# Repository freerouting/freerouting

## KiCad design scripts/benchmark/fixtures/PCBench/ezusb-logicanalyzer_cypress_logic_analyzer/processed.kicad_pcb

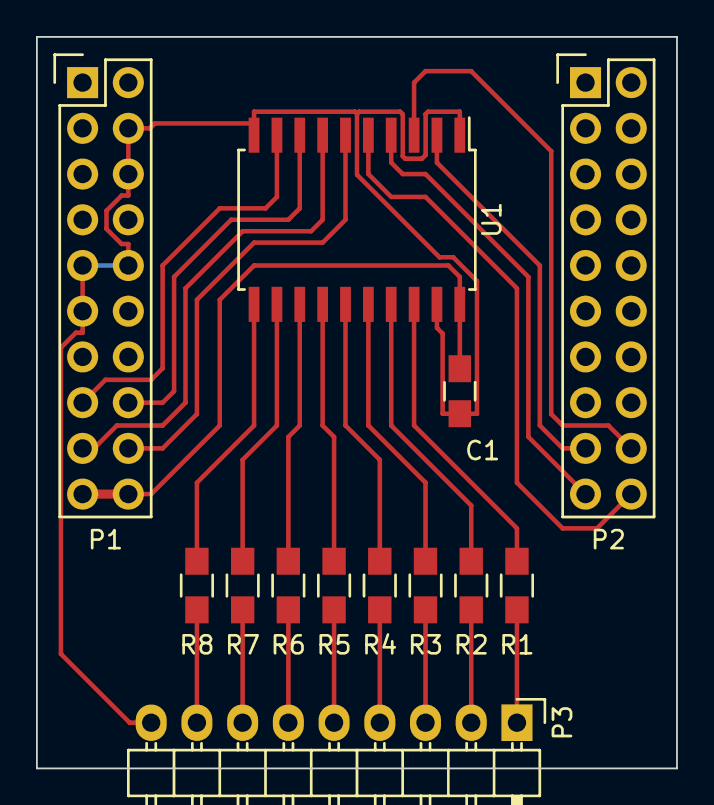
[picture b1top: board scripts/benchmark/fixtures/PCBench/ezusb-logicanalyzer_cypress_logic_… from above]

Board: 2 copper layers, 35.6 x 40.6 mm, 13 parts (0 on the bottom side), 26 nets.

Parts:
C1: .1uF; C_0805_HandSoldering
P1, P2: CONN_02X10; Pin_Header_Straight_2x10
P3: CONN_01X09; Pin_Header_Angled_1x09
R1, R2, R3, R4, R5, R6, R7, R8: 100; R_0805_HandSoldering
U1: 74LCX245; SOIC-20_7.5x12.8mm_Pitch1.27mm

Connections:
/PB0: P1.15, U1.9
/PB1: P1.16, U1.8
/PB2: P1.17, U1.7
/PB3: P1.18, U1.6
/PB4: P2.20, U1.5
/PB5: P2.19, U1.4
/PB6: P2.18, U1.3
/PB7: P2.17, U1.2
GND: C1.2, P1.4, P1.6, P1.9, P1.10, P1.11, P3.9, U1.1, U1.10, U1.19
unnamed: P3.1, R1.2
unnamed: P3.2, R2.2
unnamed: P3.3, R3.2
unnamed: P3.4, R4.2
unnamed: P3.5, R5.2
unnamed: P3.6, R6.2
unnamed: P3.7, R7.2
unnamed: P3.8, R8.2
unnamed: R1.1, U1.18
unnamed: R2.1, U1.17
unnamed: R3.1, U1.16
unnamed: R4.1, U1.15
unnamed: R5.1, U1.14
unnamed: R6.1, U1.13
unnamed: R7.1, U1.12
unnamed: R8.1, U1.11
VCC: C1.1, P1.19, P1.20, U1.20

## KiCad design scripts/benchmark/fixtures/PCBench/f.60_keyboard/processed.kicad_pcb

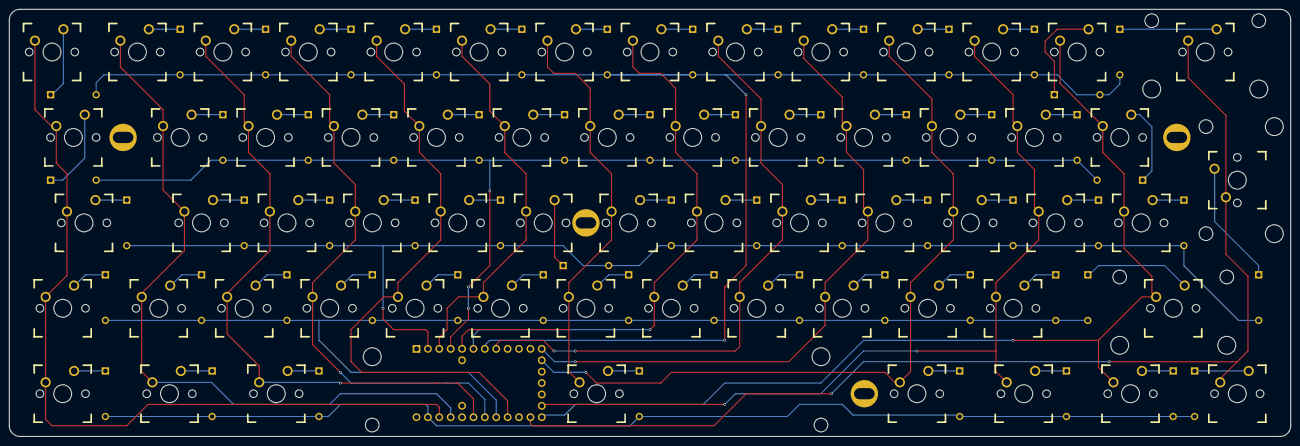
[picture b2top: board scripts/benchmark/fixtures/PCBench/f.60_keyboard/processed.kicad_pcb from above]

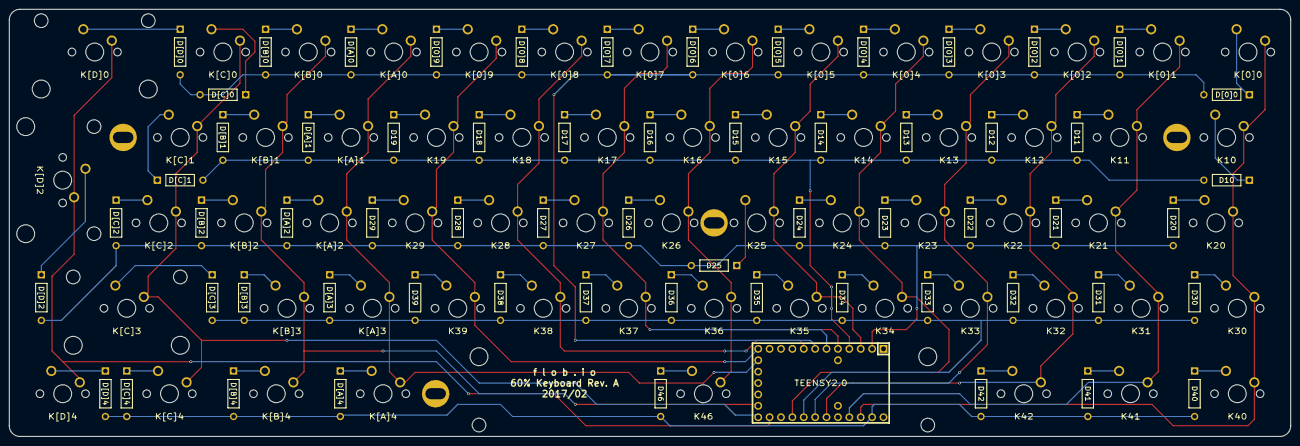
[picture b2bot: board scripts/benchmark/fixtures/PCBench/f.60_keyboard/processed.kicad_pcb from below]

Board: 2 copper layers, 285.8 x 95.3 mm, 129 parts (63 on the bottom side), 81 nets.

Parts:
D10, D11, D12, D13, D14, D15, D16, D17, D18, D19, D20, D21, D22, D23, D24, D25, D26, D27, D28, D29, D30, D31, D32, D33, D34, D35, D36, D37, D38, D39, D40, D41, D42, D46: D; DIODE
D[0]0, D[0]1, D[0]2, D[0]3, D[0]4, D[0]5, D[0]6, D[0]7, D[0]8, D[0]9: D; DIODE
D[A]0, D[A]1, D[A]2, D[A]3, D[A]4: D; DIODE
D[B]0, D[B]1, D[B]2, D[B]3, D[B]4: D; DIODE
D[C]0, D[C]1, D[C]2, D[C]3, D[C]4: D; DIODE
D[D]0, D[D]2, D[D]4: D; DIODE
K10: Tab; CHERRY_PCB_150H
K11: Q; CHERRY_PCB_100H
K12: W; CHERRY_PCB_100H
K13: E; CHERRY_PCB_100H
K14: R; CHERRY_PCB_100H
K15: T; CHERRY_PCB_100H
K16: Y; CHERRY_PCB_100H
K17: U; CHERRY_PCB_100H
K18: I; CHERRY_PCB_100H
K19: O; CHERRY_PCB_100H
K20: CapsLock; CHERRY_PCB_175H
K21: A; CHERRY_PCB_100H
K22: S; CHERRY_PCB_100H
K23: D; CHERRY_PCB_100H
K24: F; CHERRY_PCB_100H
K25: G; CHERRY_PCB_100H
K26: H; CHERRY_PCB_100H
K27: J; CHERRY_PCB_100H
K28: K; CHERRY_PCB_100H
K29: L; CHERRY_PCB_100H
K30: LShift; CHERRY_PCB_125H
K31: \; CHERRY_PCB_100H
K32: Z; CHERRY_PCB_100H
K33: X; CHERRY_PCB_100H
K34: C; CHERRY_PCB_100H
K35: V; CHERRY_PCB_100H
K36: B; CHERRY_PCB_100H
K37: N; CHERRY_PCB_100H
K38: M; CHERRY_PCB_100H
K39: ,; CHERRY_PCB_100H
K40: LCtrl; CHERRY_PCB_125H
K41: LSuper; CHERRY_PCB_125H
K42: LAlt; CHERRY_PCB_125H
K46: Space; CHERRY_PCB_625H
K[0]0: Esc; CHERRY_PCB_100H
K[0]1: 1; CHERRY_PCB_100H
K[0]2: 2; CHERRY_PCB_100H
K[0]3: 3; CHERRY_PCB_100H
K[0]4: 4; CHERRY_PCB_100H
K[0]5: 5; CHERRY_PCB_100H
K[0]6: 6; CHERRY_PCB_100H
K[0]7: 7; CHERRY_PCB_100H
K[0]8: 8; CHERRY_PCB_100H
K[0]9: 9; CHERRY_PCB_100H
K[A]0: 0; CHERRY_PCB_100H
K[A]1: P; CHERRY_PCB_100H
K[A]2: ;; CHERRY_PCB_100H
K[A]3: .; CHERRY_PCB_100H
K[A]4: RAltGr; CHERRY_PCB_125H
K[B]0: -; CHERRY_PCB_100H
K[B]1: [; CHERRY_PCB_100H
K[B]2: '; CHERRY_PCB_100H
K[B]3: /; CHERRY_PCB_100H
K[B]4: RSuper; CHERRY_PCB_125H
K[C]0: =; CHERRY_PCB_100H
K[C]1: ]; CHERRY_PCB_100H
K[C]2: #; CHERRY_PCB_100H
K[C]3: RShift; CHERRY_PCB_275H
K[C]4: Menu; CHERRY_PCB_125H
K[D]0: Backspace; CHERRY_PCB_200H
K[D]2: Enter; CHERRY_PCB_ISOR
K[D]4: RCtrl; CHERRY_PCB_125H
MH1, MH2, MH3, MH4: Poker_oval_hole
U1: TEENSY2.0; Teensy_20

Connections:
/C0: K10.2, K20.2, K30.2, K40.2, K[0]0.2, U1.27
/C1: K11.2, K21.2, K31.2, K41.2, K[0]1.2, U1.26
/C2: K12.2, K22.2, K32.2, K42.2, K[0]2.2, U1.24
/C3: K13.2, K23.2, K33.2, K[0]3.2, U1.23
/C4: K14.2, K24.2, K34.2, K[0]4.2, U1.21
/C5: K15.2, K25.2, K35.2, K[0]5.2, U1.3
/C6: K16.2, K26.2, K36.2, K46.2, K[0]6.2, U1.5
/C7: K17.2, K27.2, K37.2, K[0]7.2, U1.6
/C8: K18.2, K28.2, K38.2, K[0]8.2, U1.8
/C9: K19.2, K29.2, K39.2, K[0]9.2, U1.12
/C10: K[A]0.2, K[A]1.2, K[A]2.2, K[A]3.2, K[A]4.2, U1.13
/C11: K[B]0.2, K[B]1.2, K[B]2.2, K[B]3.2, K[B]4.2, U1.17
/C12: K[C]0.2, K[C]1.2, K[C]2.2, K[C]3.2, K[C]4.2, U1.18
/C13: K[D]0.2, K[D]2.2, K[D]4.2, U1.19
/R0: D[0]0.1, D[0]1.1, D[0]2.1, D[0]3.1, D[0]4.1, D[0]5.1, D[0]6.1, D[0]7.1, D[0]8.1, D[0]9.1, D[A]0.1, D[B]0.1, D[C]0.1, D[D]0.1, U1.7
/R1: D10.1, D11.1, D12.1, D13.1, D14.1, D15.1, D16.1, D17.1, D18.1, D19.1, D[A]1.1, D[B]1.1, D[C]1.1, U1.4
/R2: D20.1, D21.1, D22.1, D23.1, D24.1, D25.1, D26.1, D27.1, D28.1, D29.1, D[A]2.1, D[B]2.1, D[C]2.1, D[D]2.1, U1.2
/R3: D30.1, D31.1, D32.1, D33.1, D34.1, D35.1, D36.1, D37.1, D38.1, D39.1, D[A]3.1, D[B]3.1, D[C]3.1, U1.22
/R4: D40.1, D41.1, D42.1, D46.1, D[A]4.1, D[B]4.1, D[C]4.1, D[D]4.1, U1.28
unnamed: D10.2, K10.1
unnamed: D11.2, K11.1
unnamed: D12.2, K12.1
unnamed: D13.2, K13.1
unnamed: D14.2, K14.1
unnamed: D15.2, K15.1
unnamed: D16.2, K16.1
unnamed: D17.2, K17.1
unnamed: D18.2, K18.1
unnamed: D19.2, K19.1
unnamed: D20.2, K20.1
unnamed: D21.2, K21.1
unnamed: D22.2, K22.1
unnamed: D23.2, K23.1
unnamed: D24.2, K24.1
unnamed: D25.2, K25.1
unnamed: D26.2, K26.1
unnamed: D27.2, K27.1
unnamed: D28.2, K28.1
unnamed: D29.2, K29.1
unnamed: D30.2, K30.1
unnamed: D31.2, K31.1
unnamed: D32.2, K32.1
unnamed: D33.2, K33.1
unnamed: D34.2, K34.1
unnamed: D35.2, K35.1
unnamed: D36.2, K36.1
unnamed: D37.2, K37.1
unnamed: D38.2, K38.1
unnamed: D39.2, K39.1
unnamed: D40.2, K40.1
unnamed: D41.2, K41.1
unnamed: D42.2, K42.1
unnamed: D46.2, K46.1
unnamed: D[0]0.2, K[0]0.1
unnamed: D[0]1.2, K[0]1.1
unnamed: D[0]2.2, K[0]2.1
unnamed: D[0]3.2, K[0]3.1
unnamed: D[0]4.2, K[0]4.1
unnamed: D[0]5.2, K[0]5.1
unnamed: D[0]6.2, K[0]6.1
unnamed: D[0]7.2, K[0]7.1
unnamed: D[0]8.2, K[0]8.1
unnamed: D[0]9.2, K[0]9.1
unnamed: D[A]0.2, K[A]0.1
unnamed: D[A]1.2, K[A]1.1
unnamed: D[A]2.2, K[A]2.1
unnamed: D[A]3.2, K[A]3.1
unnamed: D[A]4.2, K[A]4.1
unnamed: D[B]0.2, K[B]0.1
unnamed: D[B]1.2, K[B]1.1
unnamed: D[B]2.2, K[B]2.1
unnamed: D[B]3.2, K[B]3.1
unnamed: D[B]4.2, K[B]4.1
unnamed: D[C]0.2, K[C]0.1
unnamed: D[C]1.2, K[C]1.1
unnamed: D[C]2.2, K[C]2.1
unnamed: D[C]3.2, K[C]3.1
unnamed: D[C]4.2, K[C]4.1
unnamed: D[D]0.2, K[D]0.1
unnamed: D[D]2.2, K[D]2.1
unnamed: D[D]4.2, K[D]4.1

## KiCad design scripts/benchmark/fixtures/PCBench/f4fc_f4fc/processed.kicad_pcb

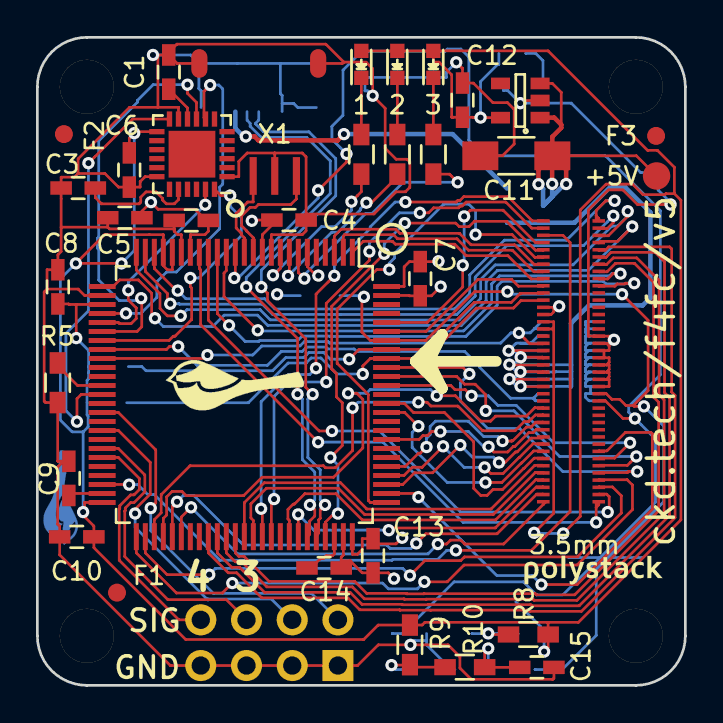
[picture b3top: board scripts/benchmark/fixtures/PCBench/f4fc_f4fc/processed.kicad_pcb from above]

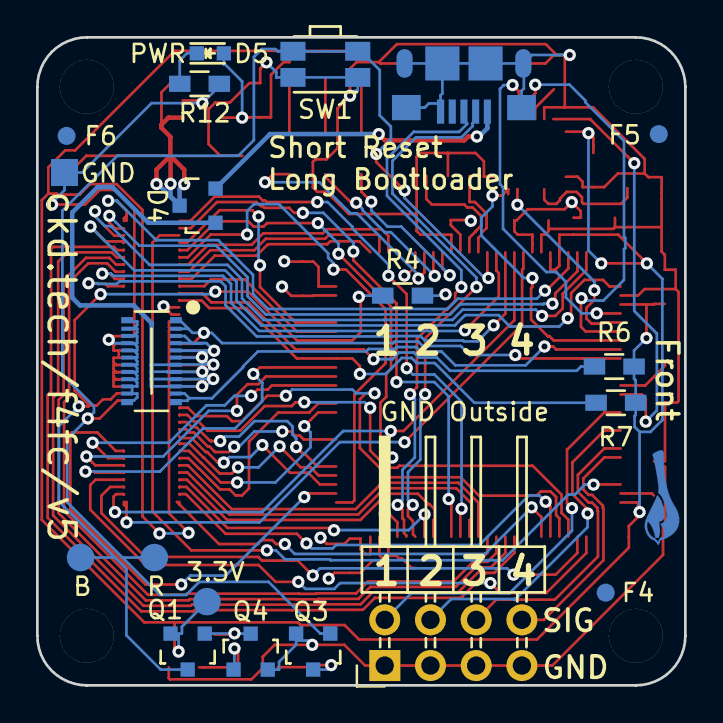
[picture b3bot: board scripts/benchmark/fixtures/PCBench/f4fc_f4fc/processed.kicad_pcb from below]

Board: 4 copper layers, 36.0 x 36.0 mm, 55 parts (20 on the bottom side), 81 nets.

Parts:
C1, C4, C6, C7, C8, C10, C13: 0.1uF; C_0603_HandSoldering
C2: 4.7uF; C_0603_HandSoldering
C3: 2.2nF; C_0603_HandSoldering
C5: 1uF; C_0603_HandSoldering
C9, C14, C15: 2.2uF; C_0603_HandSoldering
C11: 10uF+; C_1206_HandSoldering
C12: 1uF+; C_0603_HandSoldering
D1: Green; LED_0603
D2: Yellow; LED_0603
D3, D5: Red; LED_0603
D4: D_Schottky_x2_KCom_AAK; SOT-23
F1, F2, F3, F4, F5, F6: 1mm; Fiducial
P1: 3V3; Measurement_Point_Round-SMD-Pad_Small
P2: CONN_01X01; Measurement_Point_Square-SMD-Pad_Small
P3: USB_OTG; Mini-USB-B-EDGE
P4: CONN_02X04; Pin_Header_Angled_2x04
P5: CONN_02X10; DF40-20pin-Header
P6: RESET; Measurement_Point_Round-SMD-Pad_Small
P7: BOOT0; Measurement_Point_Round-SMD-Pad_Small
P9: 5V; Measurement_Point_Round-SMD-Pad_Small
PORT_OUT1: CKD_SANDWICH; DF40-3-4mm-80pin-Receptacle
Q1: Q_PMOS_GSD; SOT-23
Q3, Q4: Q_NMOS_GSD; SOT-23
R1, R2, R3, R12: 1k; R_0603_HandSoldering
R4, R5, R8: 10k; R_0603_HandSoldering
R6, R7: 4.7k; R_0603_HandSoldering
R9: 470k; R_0603_HandSoldering
R10: 100k; R_0603_HandSoldering
SW1: SW_PUSH; SW_SPST_EVQP7A
U1: MPU-6000; QFN-24-1EP_4x4mm_Pitch0.5mm
U2: STM32F40xxx; LQFP-100_14x14mm_Pitch0.5mm
U3: TLV70233DBV; SOT-23-5
X1: 8mhz; CSTCE_G-CSTCE_G_Z
svg2mod: G***; polystack-bold-0.4

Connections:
+5V: D4.1, P5.3, P5.5, P5.7, P5.9, P5.11, P5.13, P5.15, P5.17, PORT_OUT1.19, PORT_OUT1.20, PORT_OUT1.21, PORT_OUT1.22, PORT_OUT1.23, PORT_OUT1.24
+5VA: D4.2, P3.1
+BATT: P5.19, PORT_OUT1.18, U2.34
/ADC1: PORT_OUT1.49, U2.15
/ADC2: PORT_OUT1.50, U2.16
/GPIO1_14_SWCLK: PORT_OUT1.6, U2.76
/GPIO2_13_SWDIO: PORT_OUT1.5, U2.72
/GPIO3: PORT_OUT1.7, U2.3
/GPIO4: PORT_OUT1.8, U2.2
/GPIO5: PORT_OUT1.9, U2.1
/GPIO6: PORT_OUT1.10, U2.95
/LED0: R3.1, U2.7
/LED1: R2.1, U2.8
/LED2: R1.1, U2.9
/MPU_INT: U1.12, U2.38
/MPU_MISO: U1.9, U2.31
/MPU_MOSI: U1.24, U2.32
/MPU_NSS: U1.8, U2.29
/MPU_SCK: U1.23, U2.30
/Power/CURRENT: P5.1, U2.33
/Reset/BOOT0: P7.1, PORT_OUT1.65, Q1.3, R4.2, U2.94
/Reset/RESET: P6.1, PORT_OUT1.66, Q3.1, SW1.2, U2.14
/SPI1_MISO: PORT_OUT1.79, U2.17
/SPI1_MOSI: PORT_OUT1.80, U2.18
/SPI1_NSS: PORT_OUT1.77, U2.51
/SPI1_SCK: PORT_OUT1.78, U2.52
/SPI2_MISO: PORT_OUT1.75, U2.90
/SPI2_MOSI: PORT_OUT1.76, U2.91
/SPI2_NSS: PORT_OUT1.73, U2.77
/SPI2_SCK: PORT_OUT1.74, U2.89
/TIM1_CH1: P4.2, U2.40
/TIM1_CH2: P4.4, U2.42
/TIM1_CH3: P4.6, U2.44
/TIM1_CH4: P4.8, U2.45
/TIM2_CH4: PORT_OUT1.3, U2.48
/TIM3_CH4: PORT_OUT1.2, U2.66
/TIM8_CH3: PORT_OUT1.1, U2.65
/TIM11_CH1: PORT_OUT1.4, U2.96
/TIM12_CH1_UART8_RX: PORT_OUT1.28, U2.53
/TIM12_CH2_UART8_TX: PORT_OUT1.27, U2.54
/TIMG1_CH1: PORT_OUT1.41, U2.23
/TIMG1_CH2: PORT_OUT1.42, U2.24
/TIMG1_CH3: PORT_OUT1.43, U2.25
/TIMG1_CH4: PORT_OUT1.44, U2.26
/TIMG2_CH1: PORT_OUT1.45, U2.59
/TIMG2_CH2: PORT_OUT1.46, U2.60
/TIMG2_CH3: PORT_OUT1.47, U2.61
/TIMG2_CH4: PORT_OUT1.48, U2.62
/UART1_RX: PORT_OUT1.38, U2.69
/UART1_TX: PORT_OUT1.37, U2.68
/UART2_RX: PORT_OUT1.34, U2.87
/UART2_TX: PORT_OUT1.33, U2.86
/UART3_RX: PORT_OUT1.40, U2.56
/UART3_TX: PORT_OUT1.39, U2.55
/UART4_RX: PORT_OUT1.32, U2.79
/UART4_TX: PORT_OUT1.31, U2.78
/UART5_RX: PORT_OUT1.30, U2.83
/UART5_TX: PORT_OUT1.29, U2.80
/UART6_RX: PORT_OUT1.36, U2.64
/UART6_TX: PORT_OUT1.35, U2.63
/USB_D+: P3.3, U2.71
/USB_D-: P3.2, U2.70
/i2c_SCL: PORT_OUT1.12, R7.2, U2.92
/i2c_SDA: PORT_OUT1.11, R6.1, U2.93
GNDPWR: C1.2, C2.1, C3.1, C4.1, C5.1, C6.2, C7.1, C8.1, C9.2, C10.2, C11.2, C12.2, C13.1, C14.1, C15.2, P2.1, P3.5, P3.6, P4.1, P4.3, P4.5, P4.7, P5.2, P5.4, P5.6, P5.8, P5.10, P5.12, P5.14, P5.16, P5.18, P5.20, PORT_OUT1.13, PORT_OUT1.14, PORT_OUT1.57, PORT_OUT1.58, PORT_OUT1.59, PORT_OUT1.60, PORT_OUT1.61, PORT_OUT1.62, PORT_OUT1.63, PORT_OUT1.64, Q3.2, Q4.2, R4.1, R5.2, R12.2, SW1.1, U1.1, U1.11, U1.18, U2.10, U2.20, U2.27, U2.74, U2.99, U3.2, X1.3
unnamed: C1.1, U1.10
unnamed: C3.2, U1.20
unnamed: C9.1, U2.49
unnamed: C11.1, D4.3, P9.1, U3.1, U3.3
unnamed: C14.2, U2.73
unnamed: C15.1, Q4.1, R10.1
unnamed: D1.1, R1.2
unnamed: D2.1, R2.2
unnamed: D3.1, R3.2
unnamed: D5.1, R12.1
unnamed: Q1.1, Q4.3, R8.2
unnamed: Q3.3, R9.2, R10.2
unnamed: R5.1, U2.37
unnamed: U2.12, X1.1
unnamed: U2.13, X1.2
VDD: C2.2, C4.2, C5.2, C6.1, C7.2, C8.2, C10.1, C12.1, C13.2, D1.2, D2.2, D3.2, D5.2, P1.1, PORT_OUT1.15, PORT_OUT1.16, Q1.2, R6.2, R7.1, R8.1, R9.1, U1.13, U2.6, U2.11, U2.19, U2.21, U2.22, U2.28, U2.50, U2.75, U2.100, U3.5

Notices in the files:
scripts/benchmark/fixtures/PCBench/ezusb-logicanalyzer_cypress_logic_analyzer/processed.kicad_pcb:
Creative Commons BY-SA
scripts/benchmark/fixtures/PCBench/f4fc_f4fc/processed.kicad_pcb:
Copyright 2016 Chickadee Tech LLC,
This work is licensed under the Creative Commons Attribution 4.0 International License.
To view a copy of this license, visit http://creativecommons.org/licenses/by/4.0
or send a letter to Creative Commons, PO Box 1866, Mountain View, CA 94042, USA.
